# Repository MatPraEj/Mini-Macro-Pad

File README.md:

# Mini-Macro-Pad

Mini macropad is a 6 key "macropad" with a rotary encoder and OLED Display to allow for flexibility and the very important cool factor :D.

Why macropad in ""? Although it can function as a macropad when used with VIA, its main purpose is to act as a second mini keyboard with the RCTL, RSFT, LEFT, UP, DOWN, RIGHT buttons to serve as a sort of controller for PC where the second player plays on arrow keys and two buttons!

## Features:
- a Sturdy case with multiple points where the PCB is supported to minimize flex
- a recessed USB-C port
- an EC11 Rotary encoder for versatilty
- a 32x128 OLED display for cool factor
- 6 keys
- and [VIA](https://www.caniusevia.com/) support

## CAD Model
The Mini macropad is put together using 4 M3x16mm bolts and 4 heatset inserts, with another 1 M3x6 bolt holding the PCB (there are slots for 3 if it turns out 1 is unstable)

There are 3 seperate pieces of the case: the bottom where the PCB sits on a raised ledge around the edges as well as center supports; the middle part that acts as the plate for keyswitches, it is 3mm thick to allow for sturdiness but has a recess around the switch holes so they can clip in; and the top which covers the middle plate and sits flush with the bottom of the keycaps.

Learning Fusion 360 was a bit of a pain but I got the hang of it, now I can describe my experience only with one word: Nifty.

## PCB
Below is my PCB made in KiCad, Joe Scotto's guide's came in incredibly handy with this one.

I also snuck in a silkscreen easter egg of a sketch of the mini macropad :D

Schematic:

PCB:

## Firmware
I used [QMK](https://qmk.fm/) for the firmware here, it was a massive pain to setup but if VIA works (fingers crossed!) it will be worth it, if it doesn't I'll do whatever to make it work.

By default:
- the rotary encoder changes volume and mutes/unmutes media when pressed
- the 6 keys act as a mini gamepad posing as UP, DOWN, LEFT, RIGHT and RCTL and RSFT
- the OLED screen displays an animation of a seal (by request of a friend)

VIA will allow me to change these keyboard mappings, allowing flexibility and allowing me to use it as an actual macropad :D

## BOM
Below is everything I'll need to build this:
- 6x Cherry MX Switches
- 6x DSA Keycaps
- 4x M3x5x4 Heatset inserts
- 4x M3x16 SHCS Bolts
- 1x M3x6 SHCS Bolt (I will source this myself)
- 7x DO-35 Diodes
- 1x 0.91" 128x32 OLED Display
- 1x EC11 Rotary Encoder
- 1x Seed Studio XIAO RP2040
- 2x 2.54mm 1x7 pin headers
- 1x 2.54mm 1x4 pin header
- 1x Case (3 3d printed parts)
- 1x Custom PCB

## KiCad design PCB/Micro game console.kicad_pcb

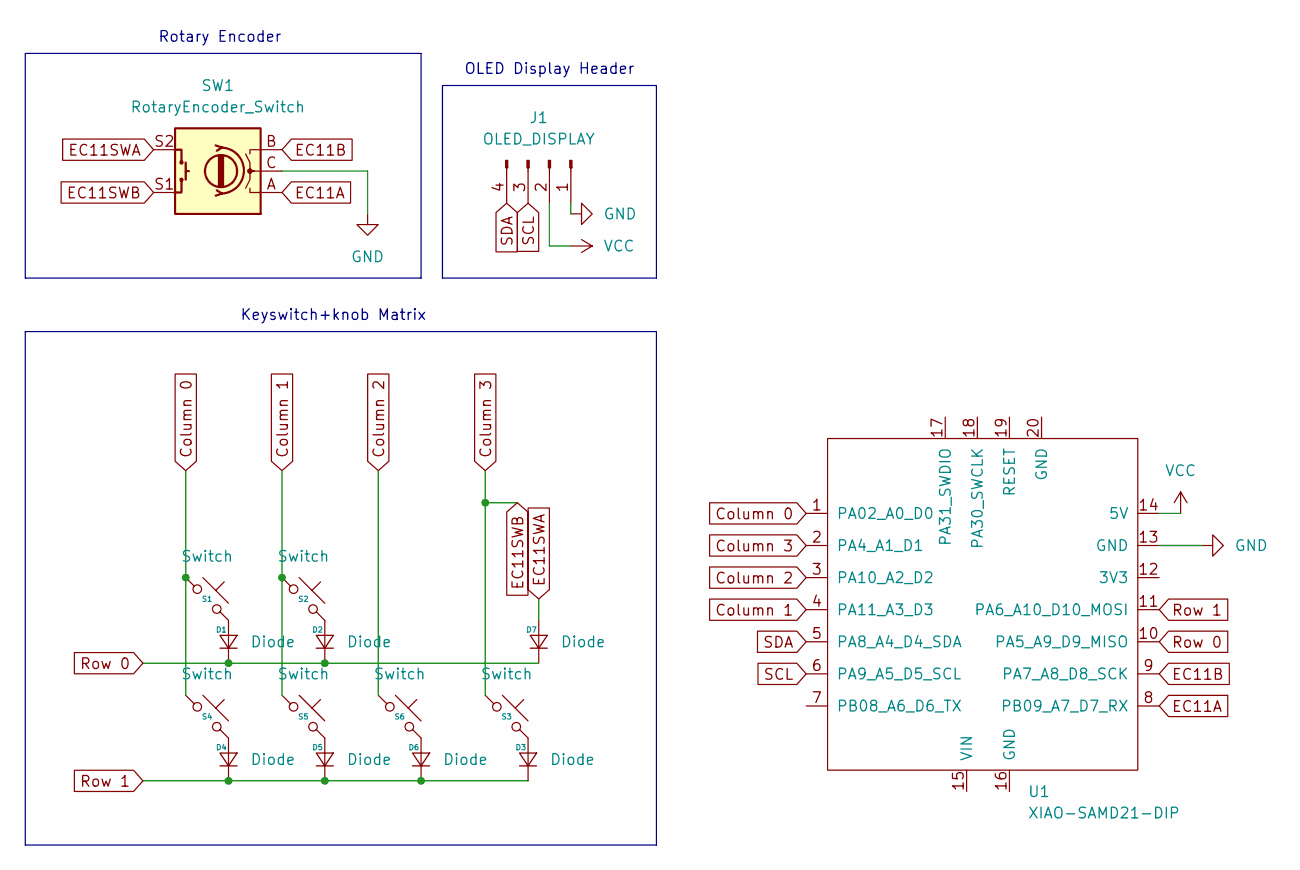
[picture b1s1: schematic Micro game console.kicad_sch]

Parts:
D1, D2, D3, D4, D5, D6, D7: Diode; Diode_DO-35
J1: OLED_DISPLAY; SSD1306-0.91-OLED-4pin-128x32
S1, S2, S3, S4, S5, S6: Switch; MX_PCB_1.00u
SW1: RotaryEncoder_Switch; RotaryEncoder_Alps_EC11E-Switch_Vertical_H20mm
U1: XIAO-SAMD21-DIP

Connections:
Column 0: S1.1, S4.1, U1.1 (PA02_A0_D0)
Column 1: S2.1, S5.1, U1.4 (PA11_A3_D3)
Column 2: S6.1, U1.3 (PA10_A2_D2)
Column 3: S3.1, SW1.S1, U1.2 (PA4_A1_D1)
EC11A: SW1.A, U1.8 (PB09_A7_D7_RX)
EC11B: SW1.B, U1.9 (PA7_A8_D8_SCK)
EC11SWA: D7.2 (A), SW1.S2
GND: J1.1, SW1.C, U1.13 (GND)
unnamed: D1.2 (A), S1.2
unnamed: D2.2 (A), S2.2
unnamed: D3.2 (A), S3.2
unnamed: D4.2 (A), S4.2
unnamed: D5.2 (A), S5.2
unnamed: D6.2 (A), S6.2
Row 0: D1.1 (K), D2.1 (K), D7.1 (K), U1.10 (PA5_A9_D9_MISO)
Row 1: D3.1 (K), D4.1 (K), D5.1 (K), D6.1 (K), U1.11 (PA6_A10_D10_MOSI)
SCL: J1.3, U1.6 (PA9_A5_D5_SCL)
SDA: J1.4, U1.5 (PA8_A4_D4_SDA)
VCC: J1.2, U1.14 (5V)

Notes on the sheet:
OLED Display Header
Rotary Encoder
Keyswitch+knob Matrix

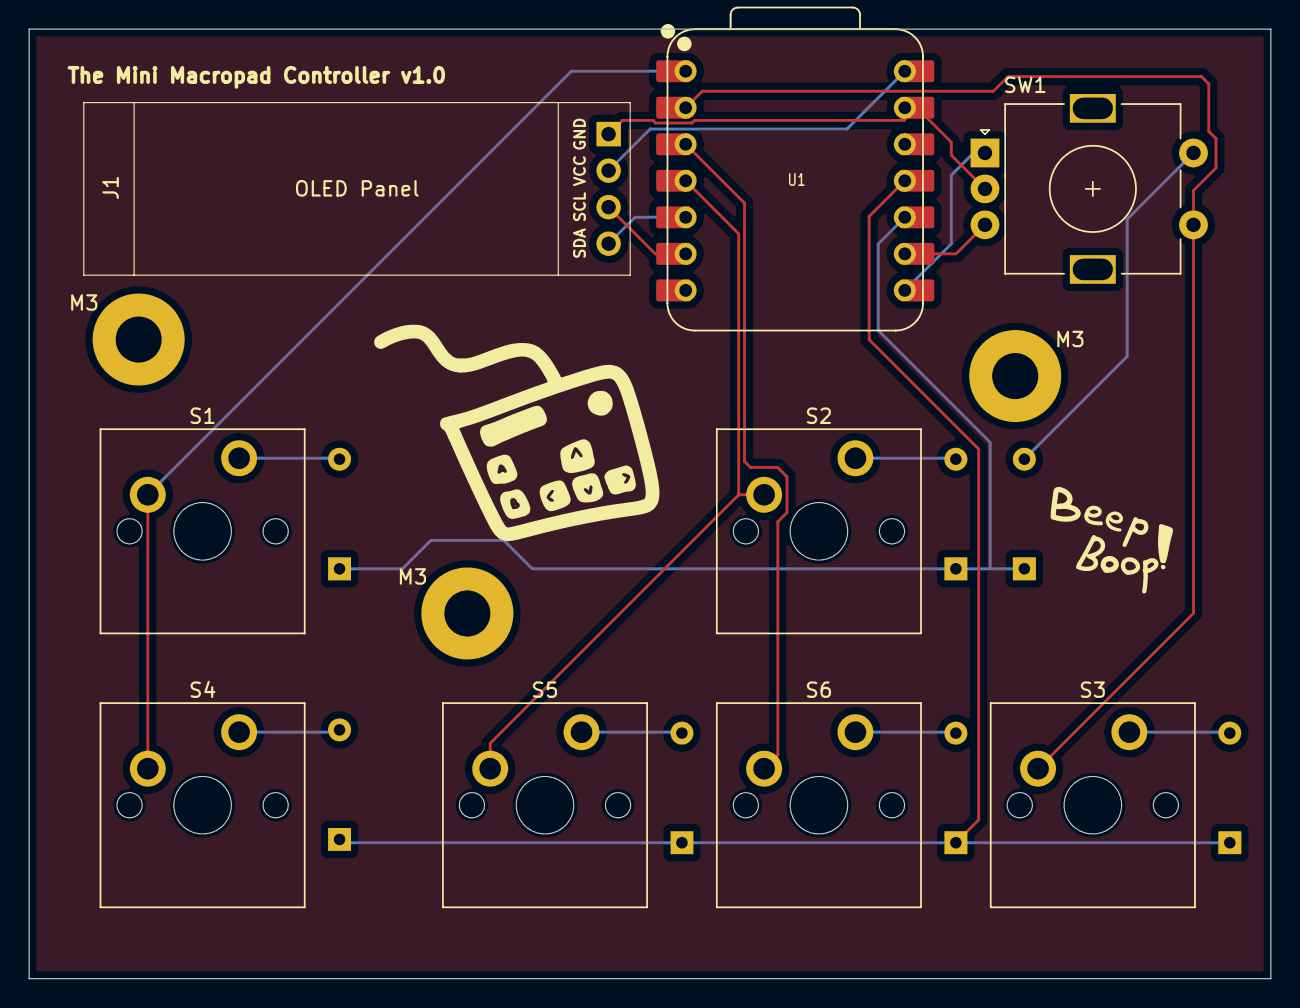
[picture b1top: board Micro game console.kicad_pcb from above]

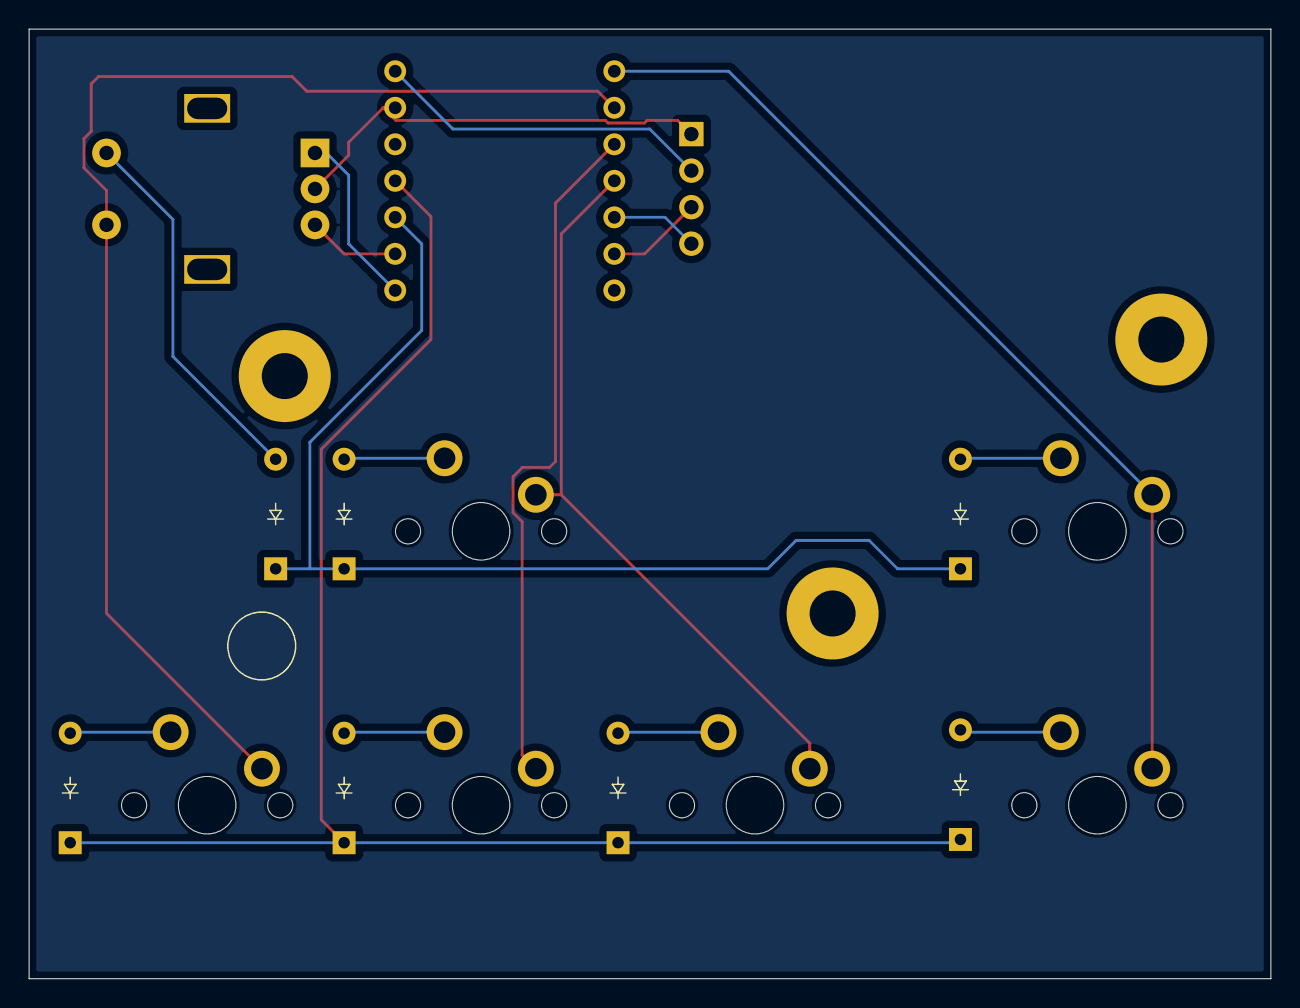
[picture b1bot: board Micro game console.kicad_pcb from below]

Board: 2 copper layers, 86.4 x 66.0 mm, 20 parts (7 on the bottom side), 19 nets.

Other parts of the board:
M3, M3#2, M3#3: MountingHole_3.2mm_M3_Pad
sdasd: LOGO; beep_boop

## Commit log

2026-02-10 Added readme assets
    still missing screenshot of how pieces fit together
2026-02-10 Added Mini macropad's STEP file
2026-02-10 Added PCB files to the PCB folder
2026-02-10 Add default keymap and OLED animation support
    This file defines a keymap for a keyboard layout and includes OLED animation rendering functionality.
2026-02-10 Enhanced README
2026-02-10 Fix formatting for Schematic and PCB sections
